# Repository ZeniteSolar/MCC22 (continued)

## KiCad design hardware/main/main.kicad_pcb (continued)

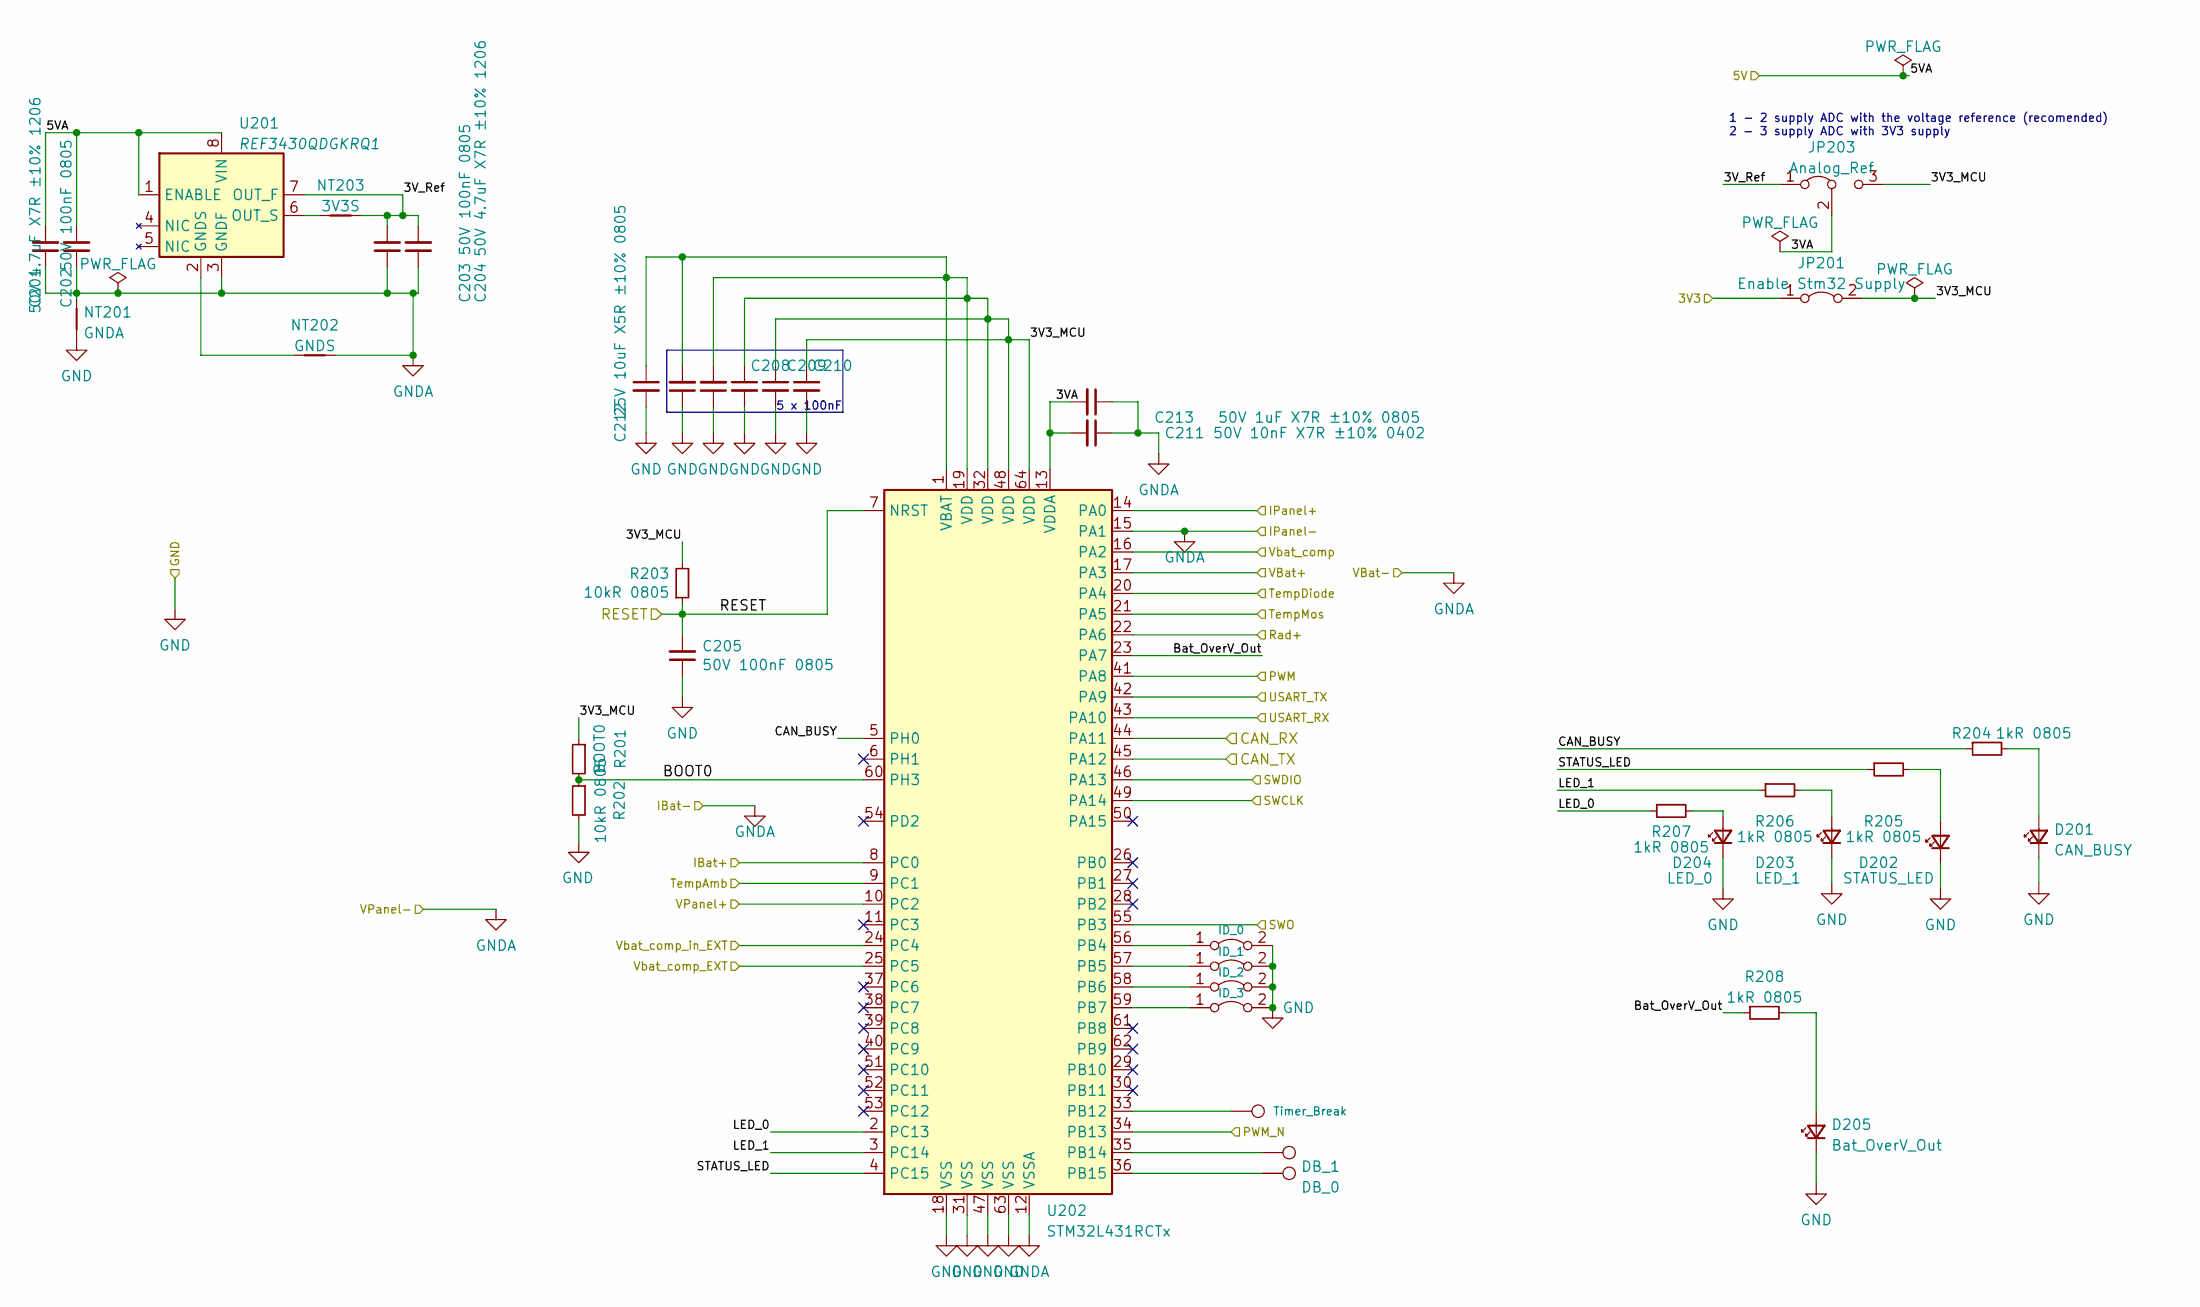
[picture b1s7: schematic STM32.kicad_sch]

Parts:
C201, C204: 50V 4.7uF X7R ±10% 1206; C_1206_3216Metric_Pad1.33x1.80mm_HandSolder
C202, C203, C205, C206, C207: 50V 100nF 0805; C_0805_2012Metric_Pad1.18x1.45mm_HandSolder
C208, C209, C210: 50V 100nF X7R ±10% 0402; C_0402_1005Metric_Pad0.74x0.62mm_HandSolder
C211: 50V 10nF X7R ±10% 0402; C_0402_1005Metric_Pad0.74x0.62mm_HandSolder
C212: 25V 10uF X5R ±10% 0805; C_0805_2012Metric_Pad1.18x1.45mm_HandSolder
C213: 50V 1uF X7R ±10% 0805; C_0805_2012Metric_Pad1.18x1.45mm_HandSolder
D201: CAN_BUSY; LED_0805_2012Metric_Pad1.15x1.40mm_HandSolder
D202: STATUS_LED; LED_0805_2012Metric_Pad1.15x1.40mm_HandSolder
D203: LED_1; LED_0805_2012Metric_Pad1.15x1.40mm_HandSolder
D204: LED_0; LED_0805_2012Metric_Pad1.15x1.40mm_HandSolder
D205: Bat_OverV_Out; LED_0805_2012Metric_Pad1.15x1.40mm_HandSolder
JP201: Enable Stm32 Supply; SolderJumper-2_P0.5mm_Open_TrianglePad0.8x0.5mm
JP203: Analog_Ref; SolderJumper-3_P0.5mm_Open_TrianglePad0.8x0.5mm
JP204: ID_0; SolderJumper-2_P0.5mm_Open_TrianglePad0.8x0.5mm
JP205: ID_1; SolderJumper-2_P0.5mm_Open_TrianglePad0.8x0.5mm
JP206: ID_2; SolderJumper-2_P0.5mm_Open_TrianglePad0.8x0.5mm
JP207: ID_3; SolderJumper-2_P0.5mm_Open_TrianglePad0.8x0.5mm
NT201: GNDA; NetTie-2_SMD_Pad0.3mm
NT202: GNDS; NetTie-2_SMD_Pad0.3mm
NT203: 3V3S; NetTie-2_SMD_Pad0.3mm
R201: BOOT0; R_0402_1005Metric
R202, R203: 10kR 0805; R_0805_2012Metric_Pad1.20x1.40mm_HandSolder
R204, R205, R206, R207, R208: 1kR 0805; R_0805_2012Metric_Pad1.20x1.40mm_HandSolder
TP201: DB_0; TestPoint_Pad_1.0x1.0mm_small
TP202: DB_1; TestPoint_Pad_1.0x1.0mm_small
TP203: Timer_Break; TestPoint_Pad_1.0x1.0mm_small
U201: REF3430QDGKRQ1; VSSOP-8_3.0x3.0mm_P0.65mm
U202: STM32L431RCTx; LQFP-64_10x10mm_P0.5mm

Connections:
/3V3_STM: JP201.1 (A); also elsewhere on the board
/5V_STM: C201.2, C202.2, U201.1 (ENABLE), U201.8 (VIN); also elsewhere on the board
/Analog/I_bat_adc+: U202.8 (PC0); also elsewhere on the board
/Analog/I_panel_adc+: U202.14 (PA0); also elsewhere on the board
/Analog/V_Rad: U202.22 (PA6); also elsewhere on the board
/Analog/V_bat_adc+: U202.17 (PA3); also elsewhere on the board
/Analog/V_panel_adc+: U202.10 (PC2); also elsewhere on the board
/Analog/V_temp_amb: U202.9 (PC1); also elsewhere on the board
/Analog/V_temp_diode: U202.20 (PA4); also elsewhere on the board
/Analog/V_temp_mos: U202.21 (PA5); also elsewhere on the board
/Analog/Vbat_comp: U202.16 (PA2); also elsewhere on the board
/Analog/Vbat_comp_EXT: U202.25 (PC5); also elsewhere on the board
/Analog/Vbat_comp_in_EXT: U202.24 (PC4); also elsewhere on the board
/PWM: U202.41 (PA8); also elsewhere on the board
/RESET: C205.2, R203.1, U202.7 (NRST); also elsewhere on the board
/STM32/3V3_MCU: C206.2, C207.2, C208.1, C209.1, C210.1, C212.1, JP201.2 (B), JP203.3 (B), R201.1, R203.2, U202.1 (VBAT), U202.19 (VDD), U202.32 (VDD), U202.48 (VDD), U202.64 (VDD)
/STM32/3VA: C211.2, C213.2, JP203.2 (C), U202.13 (VDDA)
/STM32/3V_Ref: C203.2, C204.2, JP203.1 (A), NT203.1, U201.7 (OUT_F)
/STM32/BOOT0: R201.2, R202.1, U202.60 (PH3)
/STM32/Bat_OverV_Out: R208.1, U202.23 (PA7)
/STM32/CAN_BUSY: R204.1, U202.5 (PH0)
/STM32/CAN_RX: U202.44 (PA11); also elsewhere on the board
/STM32/CAN_TX: U202.45 (PA12); also elsewhere on the board
/STM32/LED_0: R207.1, U202.2 (PC13)
/STM32/LED_1: R206.1, U202.3 (PC14)
/STM32/PWM_N: U202.34 (PB13)
/STM32/STATUS_LED: R205.1, U202.4 (PC15)
/SWCLK: U202.49 (PA14); also elsewhere on the board
/SWDIO: U202.46 (PA13); also elsewhere on the board
/SWO: U202.55 (PB3); also elsewhere on the board
/USART_RX: U202.43 (PA10); also elsewhere on the board
/USART_TX: U202.42 (PA9); also elsewhere on the board
GND: C205.1, C206.1, C207.1, C208.2, C209.2, C210.2, C212.2, D201.1 (K), D202.1 (K), D203.1 (K), D204.1 (K), D205.1 (K), JP204.2 (B), JP205.2 (B), JP206.2 (B), JP207.2 (B), NT201.2, R202.2, U202.18 (VSS), U202.31 (VSS), U202.47 (VSS), U202.63 (VSS); also elsewhere on the board
GNDA: C201.1, C202.1, C203.1, C204.1, C211.1, C213.1, NT201.1, NT202.1, U201.3 (GNDF), U202.12 (VSSA), U202.15 (PA1); also elsewhere on the board
unnamed: D201.2 (A), R204.2
unnamed: D202.2 (A), R205.2
unnamed: D203.2 (A), R206.2
unnamed: D204.2 (A), R207.2
unnamed: D205.2 (A), R208.2
unnamed: JP204.1 (A), U202.56 (PB4)
unnamed: JP205.1 (A), U202.57 (PB5)
unnamed: JP206.1 (A), U202.58 (PB6)
unnamed: JP207.1 (A), U202.59 (PB7)
unnamed: NT202.2, U201.2 (GNDS)
unnamed: NT203.2, U201.6 (OUT_S)
unnamed: TP201.1, U202.36 (PB15)
unnamed: TP202.1, U202.35 (PB14)
unnamed: TP203.1, U202.33 (PB12)

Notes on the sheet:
1 - 2 supply ADC with the voltage reference (recomended) 2 - 3 supply ADC with 3V3 supply
5 x 100nF

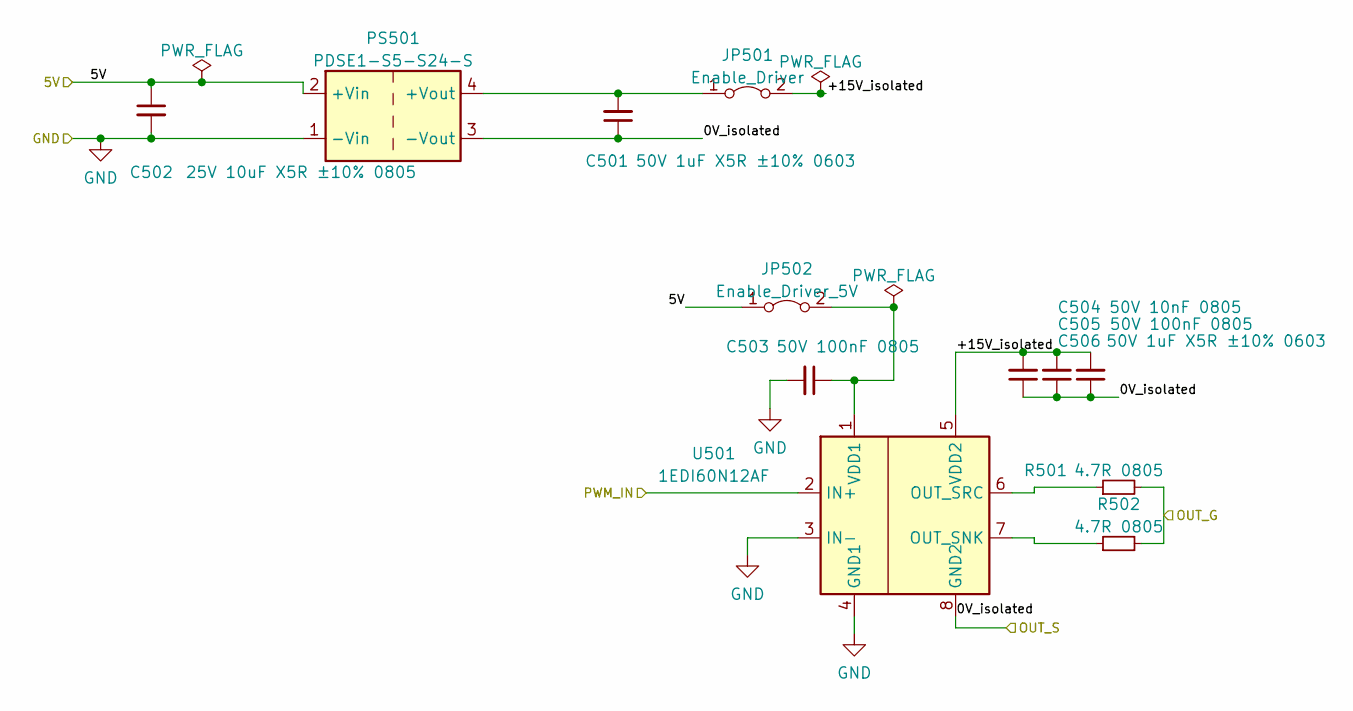
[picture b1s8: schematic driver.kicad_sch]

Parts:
C501, C506: 50V 1uF X5R ±10% 0603; C_0603_1608Metric_Pad1.08x0.95mm_HandSolder
C502: 25V 10uF X5R ±10% 0805; C_0805_2012Metric_Pad1.18x1.45mm_HandSolder
C503, C505: 50V 100nF 0805; C_0805_2012Metric_Pad1.18x1.45mm_HandSolder
C504: 50V 10nF 0805; C_0805_2012Metric_Pad1.18x1.45mm_HandSolder
JP501: Enable_Driver; SolderJumper-2_P0.5mm_Open_TrianglePad0.8x0.5mm
JP502: Enable_Driver_5V; SolderJumper-2_P0.5mm_Open_TrianglePad0.8x0.5mm
PS501: PDSE1-S5-S24-S; Converter_DCDC_Murata_MEE3SxxxxSC_THT
R501, R502: 4.7R 0805; R_0805_2012Metric_Pad1.20x1.40mm_HandSolder
U501: 1EDI60N12AF; SOIC-8_3.9x4.9mm_P1.27mm

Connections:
/5V_Driver: C502.1, JP502.1 (A), PS501.2 (+Vin); also elsewhere on the board
/Cuk/PWM_IN: U501.2 (IN+); also elsewhere on the board
/Cuk/S: C501.1, C504.1, C505.1, C506.1, PS501.3 (-Vout), U501.8 (GND2); also elsewhere on the board
/Cuk/driver/+15V_isolated: C504.2, C505.2, C506.2, JP501.2 (B), U501.5 (VDD2)
/Cuk/driver/OUT_G: R501.2, R502.2; also elsewhere on the board
GND: C502.2, C503.2, PS501.1 (-Vin), U501.3 (IN-), U501.4 (GND1); also elsewhere on the board
unnamed: C501.2, JP501.1 (A), PS501.4 (+Vout)
unnamed: C503.1, JP502.2 (B), U501.1 (VDD1)
unnamed: R501.1, U501.6 (OUT_SRC)
unnamed: R502.1, U501.7 (OUT_SNK)

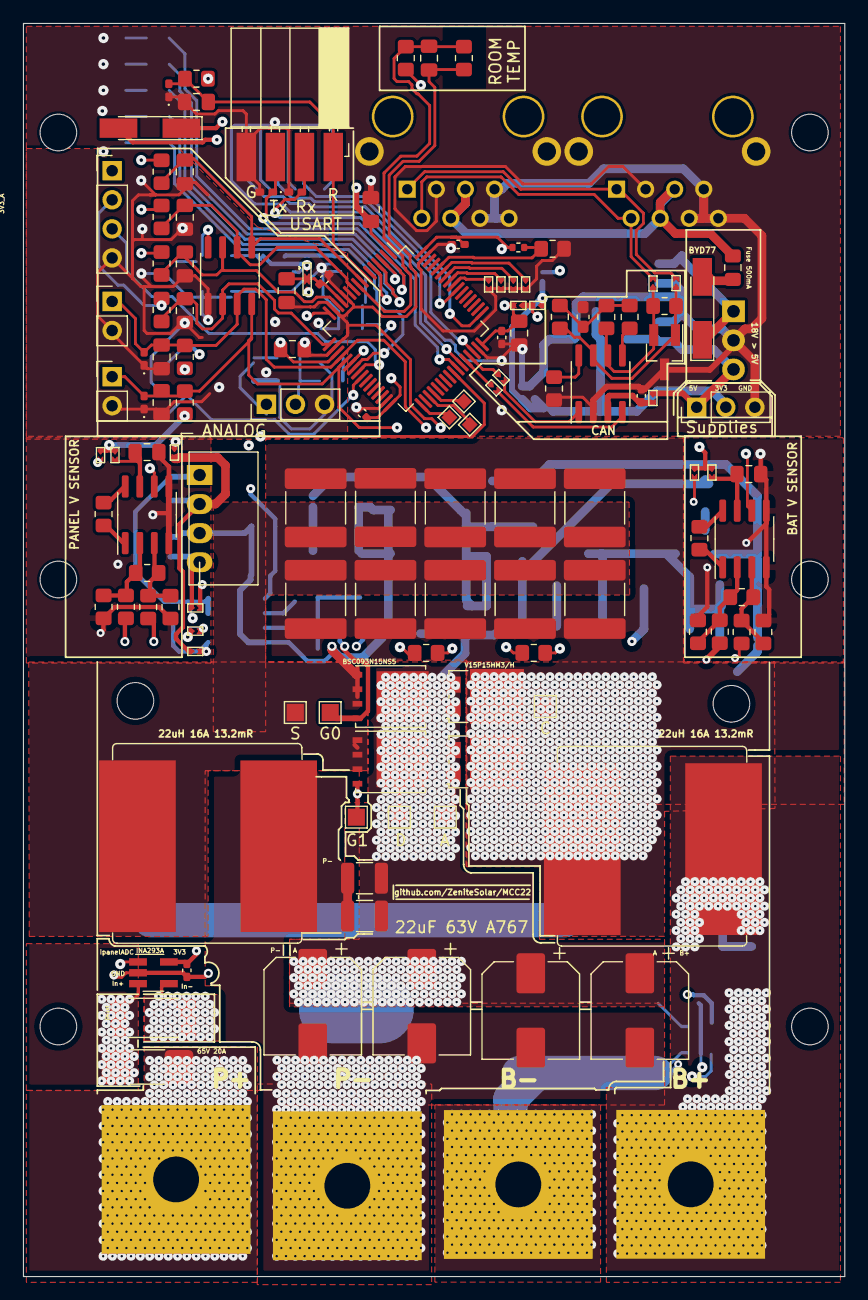
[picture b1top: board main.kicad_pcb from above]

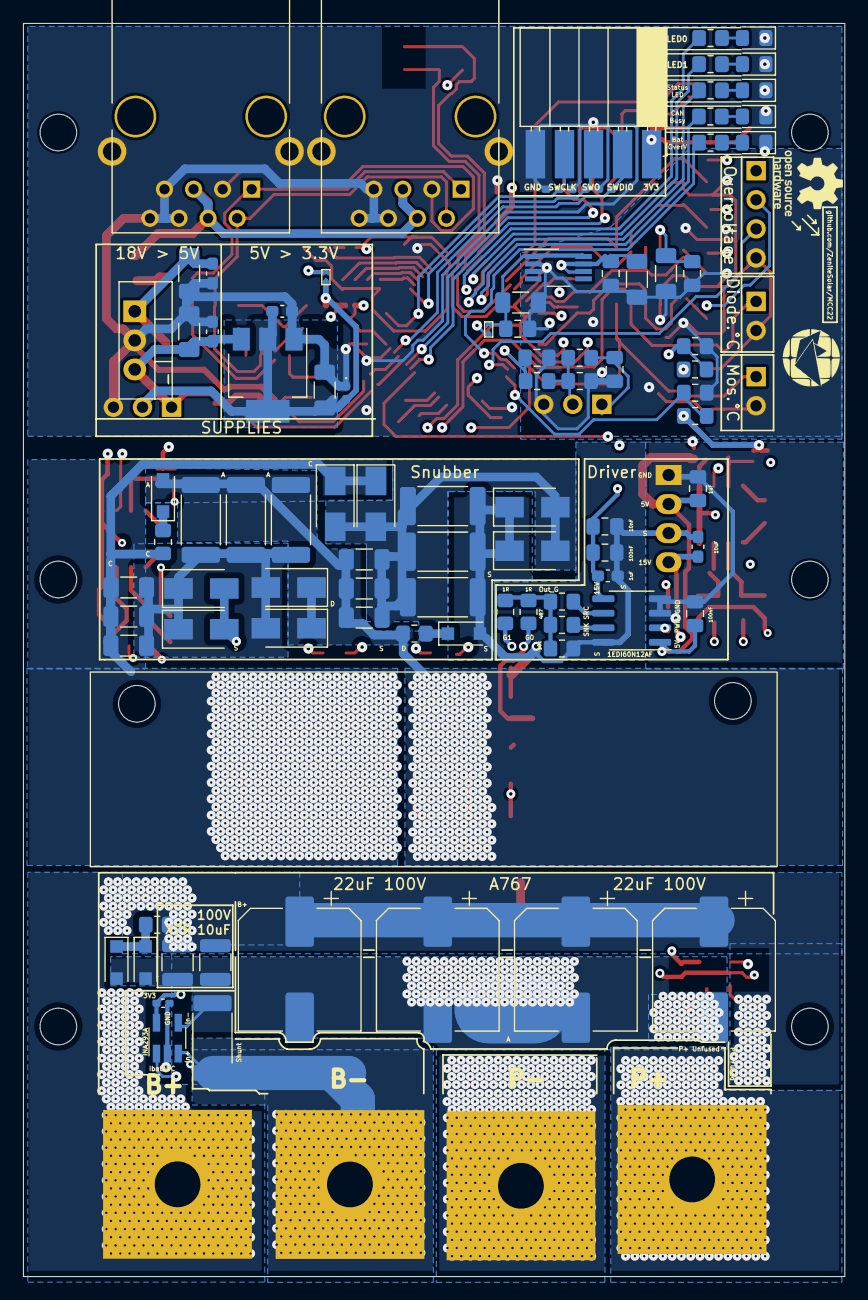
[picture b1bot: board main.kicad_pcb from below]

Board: 4 copper layers, 71.8 x 109.5 mm, 237 parts (100 on the bottom side), 108 nets.

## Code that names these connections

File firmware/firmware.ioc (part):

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Mcu.Name=STM32L431R(B-C)Tx
Mcu.Package=LQFP64
Mcu.UserName=STM32L431RCTx
PA0.GPIOParameters=GPIO_Label
PA0.GPIO_Label=IPanel+
PA0.Signal=ADCx_IN5
PA10.Mode=Asynchronous
PA10.Signal=USART1_RX
PA11.Mode=CAN_Activate
PA11.Signal=CAN1_RX
PA12.Mode=CAN_Activate
PA12.Signal=CAN1_TX
PA13\ (JTMS-SWDIO).Mode=Trace_Asynchronous_SW
PA13\ (JTMS-SWDIO).Signal=SYS_JTMS-SWDIO
PA14\ (JTCK-SWCLK).Mode=Trace_Asynchronous_SW
PA14\ (JTCK-SWCLK).Signal=SYS_JTCK-SWCLK
PA2.GPIOParameters=GPIO_Label
PA2.GPIO_Label=Vbat_comp
PA2.Signal=SharedAnalog_PA2
PA3.GPIOParameters=GPIO_Label
PA3.GPIO_Label=Vbat+
PA3.Signal=SharedAnalog_PA3
PA4.GPIOParameters=GPIO_Label
PA4.GPIO_Label=TempDiode
PA4.Signal=ADCx_IN9
PA5.GPIOParameters=GPIO_Label
PA5.GPIO_Label=TempMos
PA5.Signal=ADCx_IN10
PA6.GPIOParameters=GPIO_Label
PA6.GPIO_Label=Rad+
PA6.Signal=ADCx_IN11
PA7.GPIOParameters=GPIO_Label
PA7.GPIO_Label=Bat_OverV_Out
PA7.Mode=ExternalOutput
PA7.Signal=COMP2_OUT
PA8.GPIOParameters=GPIO_Label
PA8.GPIO_Label=PWM
PA8.Signal=S_TIM1_CH1
PA9.Mode=Asynchronous
PA9.Signal=USART1_TX
PB0.GPIOParameters=GPIO_Label
PB0.GPIO_Label=Bat_OverV_Out_EXT
PB0.Mode=ExternalOutput
PB0.Signal=COMP1_OUT
PB12.GPIOParameters=GPIO_Label
PB12.GPIO_Label=TImer_break
PB12.Signal=TIM1_BKIN_COMP2
PB13.GPIOParameters=GPIO_Label
PB13.GPIO_Label=PWM_N
PB13.Signal=TIM1_CH1N
PB14.GPIOParameters=GPIO_Label
PB14.GPIO_Label=DB_1
PB14.Signal=GPIO_Output
PB15.GPIOParameters=GPIO_Label
PB15.GPIO_Label=DB_0
PB15.Signal=GPIO_Output
PB3\ (JTDO-TRACESWO).Mode=Trace_Asynchronous_SW
PB3\ (JTDO-TRACESWO).Signal=SYS_JTDO-SWO
PB4\ (NJTRST).GPIOParameters=GPIO_PuPd,GPIO_Label
PB4\ (NJTRST).GPIO_Label=ID_0
PB4\ (NJTRST).GPIO_PuPd=GPIO_PULLUP
PB4\ (NJTRST).Signal=GPIO_Input
PB5.GPIOParameters=GPIO_PuPd,GPIO_Label
PB5.GPIO_Label=ID_1
PB5.GPIO_PuPd=GPIO_PULLUP
PB5.Signal=GPIO_Input
PB6.GPIOParameters=GPIO_PuPd,GPIO_Label
PB6.GPIO_Label=ID_2
PB6.GPIO_PuPd=GPIO_PULLUP
PB6.Signal=GPIO_Input
PB7.GPIOParameters=GPIO_PuPd,GPIO_Label
PB7.GPIO_Label=ID_3
PB7.GPIO_PuPd=GPIO_PULLUP
PB7.Signal=GPIO_Input
PC0.GPIOParameters=GPIO_Label,GPIO_Pu
PC0.GPIO_Label=ADC_SCL
PC0.GPIO_Pu=GPIO_PULLUP
PC0.Mode=I2C
PC0.Signal=I2C3_SCL
PC1.GPIOParameters=GPIO_Label,GPIO_Pu
PC1.GPIO_Label=ADC_SDA
PC1.GPIO_Pu=GPIO_PULLUP
PC1.Mode=I2C
PC1.Signal=I2C3_SDA
PC13.GPIOParameters=GPIO_Label
PC13.GPIO_Label=LED_0
PC13.Signal=GPIO_Output
PC14-OSC32_IN\ (PC14).GPIOParameters=GPIO_Label
PC14-OSC32_IN\ (PC14).GPIO_Label=LED_1
PC14-OSC32_IN\ (PC14).Signal=GPIO_Output
PC15-OSC32_OUT\ (PC15).GPIOParameters=GPIO_Label
PC15-OSC32_OUT\ (PC15).GPIO_Label=LED_STATUS
PC15-OSC32_OUT\ (PC15).Signal=GPIO_Output
PC2.GPIOParameters=GPIO_Label
PC2.GPIO_Label=Vpanel+
PC2.Signal=ADCx_IN3
PC4.GPIOParameters=GPIO_Label
PC4.GPIO_Label=Vbat_comp_in_EXT
PC4.Mode=INM
PC4.Signal=COMP1_INM
PC5.GPIOParameters=GPIO_Label
PC5.GPIO_Label=Vbat_comp_EXT
PC5.Signal=SharedAnalog_PC5
PH0-OSC_IN\ (PH0).GPIOParameters=GPIO_Label
PH0-OSC_IN\ (PH0).GPIO_Label=LED_CAN_BUSY
PH0-OSC_IN\ (PH0).Signal=GPIO_Output
RCC.HSE_VALUE=8000000
RCC.SYSCLKFreq_VALUE=80000000
RCC.SYSCLKSource=RCC_SYSCLKSOURCE_PLLCLK
board=custom

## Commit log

2022-09-13 Add initial design optimization work.
2022-10-30 Add LTSpice simulations
2022-10-30 Add last mods to PSIM simulations.
2022-10-31 Schematics: create schematics of STM32, cuk converter, canbus, analog interface
2022-11-01 Schematics: finalize Analog Snubber and Supplies
2022-11-01 Schematics: Modified component values
2022-11-01 Schematics: Sym table and libs updated
2022-11-01 Simulation: Simulating snubber with crossing diode
2022-11-01 Firmware: config stm32 pinout
2022-11-03 Schematics: Run DRC and fix errors and some warnings, also added Zenite kicad library repo as submodule
2022-11-03 Firmware: Update STM pins
2022-11-03 gitignore: add kicad backup files
2022-11-04 Layout: Organizing components
2022-11-06 Add optimization analysis with LTSPICE non ideal components.
2022-11-07 Layout: Organizing power components
2022-11-07 Firmware: add comparator inputs in Batery Voltage and CAN Signature selector inputs
2022-11-07 Schematics: Add STM32 comparator for Battery OverVoltage
2022-11-10 Layout: Fist version of power stage
2022-11-10 Layout: oganizing components of Driver and voltage sensors
2022-11-11 Layout: Organize and initialize routing of control
2022-11-12 Schematics: Anotate testpoints
2022-11-12 Layout: Control stage routing
2022-11-13 Schematics: Switch 2 Clamp inputs for better routing
2022-11-13 Schematics: Change LED order for better pcb routing
2022-11-13 Layout: Nearly complete control stage routing
2022-11-14 Create ZeniteKicadLib submodule
2022-11-14 Layout: WIP updating control
2022-11-15 Layout: Designing thermal dissipation and optimizing control
2022-11-15 Lib: Update ZeniteKicadLib to use Heatsink and solder jumper
2022-11-15 Layout: Connect all unconected nets, and fix all DRC errors
2022-11-15 Layout: Create Copper zone under NTC temperature sensor for a better thermal coupling
2022-11-20 Layout: Silkscreen updated
2022-11-20 layout: Separating analogical power nets
2022-11-20 Layout: Place components and route analog, supplies and CAN
2022-11-22 Layout: Finalize first vesion of control (DRC ok) and modify vias for better via density
2022-11-22 Layout: create margin for mechanical fixation
2022-11-24 Layout: Update silkscreen
2022-11-24 layout: fix path of heatsink (using relative path)
2022-11-24 Update ZeniteKicadLib: Fix isolated DC/DC size and 3D shape.
2022-11-24 Fix size of isolated DC/DC converter
2022-11-24 Change board surface finish to HAL SnPb
2022-11-26 WIP: adding more compact vias
2022-11-27 Layout: finalize more compact vias
2022-11-27 Layout: Silkscreen update
2022-11-27 Layout: Fix DRC issues, fix some copper zones, copy silkscreen of 5f991268df1bec187c9dadc35024444e2526c1c0
2022-11-27 Better GNDA + silk work
2022-11-27 Fix some vias, export schematic pdf and pcb gerbers
2022-12-09 Notebook for calculation of ADC timings, results implemented in Cube
2022-12-09 verify if is not necessary shift over sample result
2023-02-16 Add some 3D images
2023-02-16 move images folder to root
2023-02-18 add tests images
2023-02-18 add tests.md explaning the tests
2023-02-18 link tests document in README
2023-03-12 Create firmware project
2023-03-12 Update gitignore
2023-03-12 Firmware: add control and machine initializers, and control and machine runners into the main loop
2023-03-12 Firmware: Create DAC functions
2023-03-12 Firmware: Implement some utils, like usart debugging information and leds utils
2023-03-12 Firmware: export uart handler for logging prints
2023-03-12 Firmware: Implement comparator for battery overvoltage protection
2023-03-12 Firmware: Implement adc average using DMA, adc initilizer and adc linearization
2023-03-12 Firmware: Implement some mppt algorithms PeO: perturb and observe Pi: is in Work in Porgress Fixed: simple constant pwm Brute_force: iterate over all pwm possibilities with a constant step
2023-03-12 Firmware: Create converter confirguration file
2023-03-12 Firmware: Implement status machine basis
2023-03-12 Firmware: Implement pwm functions like init, set frequency and duty, and get frequency and duty
2023-03-12 Firmware: implement control algorithms handler
2023-03-13 temo
2023-03-17 add hardware interactive BOM
2023-03-20 add BOM in markdown
2023-03-23 add adc linearization
2023-03-23 add control algortithm: PeO with variable step
2023-03-23 initialize pwm and adc
2023-03-23 add uart callbacks and DMA
2023-03-25 Update main and code generator to use UART
2023-03-25 create uart parser similiar to SCPI
2023-03-25 added functions to get and set control algorithms
2023-03-25 add uart commands to get and set control algorithms
2023-03-25 Update documentation of the uart adding control algorithms commands
2023-04-20 change adc frequency via uart
2023-04-20 add output overvoltage protection
2023-07-25 improve control script trating errors and added control variables print
2023-07-25 feat[UART] added reset and all measurements command
2023-07-25 feat[ADC] improve adc linearization and convert adc temperature values to Celsius
2023-07-25 feat[ADC]: added function to get the adc frequency
2023-07-25 feat[CONTROL]: improve peo and brute force algorithms
2023-07-25 fix[constants]: fixx some constants
2023-07-25 cleaning[adc]: cleaned identation in the adc file
2023-07-25 feat[LEDS]: Added animation to show the signature number when initialize the board
2023-07-25 fix[protections]: increase DAC voltage to increase the trigger voltage of the OVP
2023-07-25 fix[timming]: fix uart delay
2023-07-25 doc[test]: added how to test the board after solder
2023-07-25 design[adc]: added adc linearization jupyter
2023-07-25 feat[stmCube]: update stmCubeMx
2023-07-25 design[current sensor]: Added current sensor simulation
2023-07-25 minor changes
2023-07-25 update kicad
2023-07-25 fix[identation]: convert identation to tabs and fix some warnings
2023-07-29 working
2023-07-29 better
2023-07-30 add sweep and fix constants of peo
2023-10-16 doc: added doc for new board test
2023-12-27 feat[adc]: configure extern adc with ads111x on stmcubemx
2023-12-27 feat[adc]: change config file to ads111x configuration
2023-12-27 feat[adc]: fix some files to be compatible with new adc
2023-12-27 feat[adc]: Refactor adc file to use a extern adc
2023-12-27 feat[adc]: Refactor control and algorithms files to use extern adc
2023-12-27 feat[adc]: plot tests with new adc
2023-12-27 feat[adc]: Created ads111x lib
2023-12-27 feat[log] fixed log macro to accept multiple parameters like printf
2023-12-27 feat[adc]: remove comparator and dac
2023-12-27 fix[adc]: fixed some non void functions returning void
2024-02-26 feat(gitignore): added logs into gitignore
2024-02-26 feat(adc): tested adc and computed coefficients
2024-02-26 tests: tested different frequencies to get optimum PWM frequency
2024-02-26 freat: added overvoltage error handling
2024-02-26 freat: print power and efficiency
2024-02-26 feat: setup optimal PWM frequency
2024-02-26 feat(canbus): setup canbus timings
2024-02-26 feat(gitignore): add can lib version file into gitignore
2024-02-26 feat(can-lib): added script to update can libs
2024-02-26 fix(main): added missing semi colon
2024-02-26 feat(machine): turned public get signature function
2024-02-26 feat(canbus): added measurements and state message sender
2024-02-26 feat(cube): code generated by cube
2024-05-01 fix(canbus): saving canbus handler instead of pointer of it
2024-05-01 feat(canbus): updated mcc ids and messages from mcc19 to mcc23
2024-05-01 fix(canbus): fix board number calculation was inverting the signature
2024-05-01 feat(canbus): increase canbus task frequency
2024-05-01 fix(canbus): missing schedule next message after send message
2024-05-01 remove .lck kicad files and add it on gitignore
2024-07-16 feat(canbus): send status message on canbus
2024-07-16 feat(canbus): handle error when sending message
2024-07-16 feat: clear mailbox if full
2024-07-16 fix: check if mailbox have space for next message
2024-07-16 readme: add build instructions
2024-07-19 feat: added logs
2024-07-26 feat: added whatchdog and check if power reduced
